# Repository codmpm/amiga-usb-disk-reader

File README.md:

# Amiga USB Floppy Disk Reader

> __abandoned in favor of https://nickslabor.niteto.de/projekte/adf-copy/__

This is a PCB I've designed to work with the marvelous idea, firmware and software 
from Rob Smith: https://github.com/RobSmithDev/ArduinoFloppyDiskReader 

It's nothing fancy but has some benefits I think that do matter:

* integrated _real_ FTDI232RL for communication and AVR flashing
* Decent DC/DC converter that can handle up to 5V/1A and wide input voltage (7-36V). 
This is the more power friendly way, as some drives demand more than the 
max. 500mA USB delivers
* Switchable to USB power if desired
* ATMega 328p on board with [Optiboot](https://github.com/Optiboot/optiboot)
* Solderpads for 4-pin Molex 3.5" connector with routed VCC. So if the drive needs 12V you 
can use a 12V power source

Of course this is only a fun project and does not aim to be the _best_ solution for Rob's 
approach, but it made my life easier.

This is the first release, as the PCB's have to be tested. I'm currently waiting for the 
prototypes.

## PCB

## Contributing

1. Fork it!
2. Create your feature branch: `git checkout -b my-new-feature`
3. Commit your changes: `git commit -am 'Add some feature'`
4. Push to the branch: `git push origin my-new-feature`
5. Submit a pull request :D

## Credits
Patrik Mayer, cod.m GmbH, 2019 

Rob Smith, who had the initial idea and wrote the software this is using

## License
[CC-BY-SA](https://creativecommons.org/licenses/by-sa/3.0/)

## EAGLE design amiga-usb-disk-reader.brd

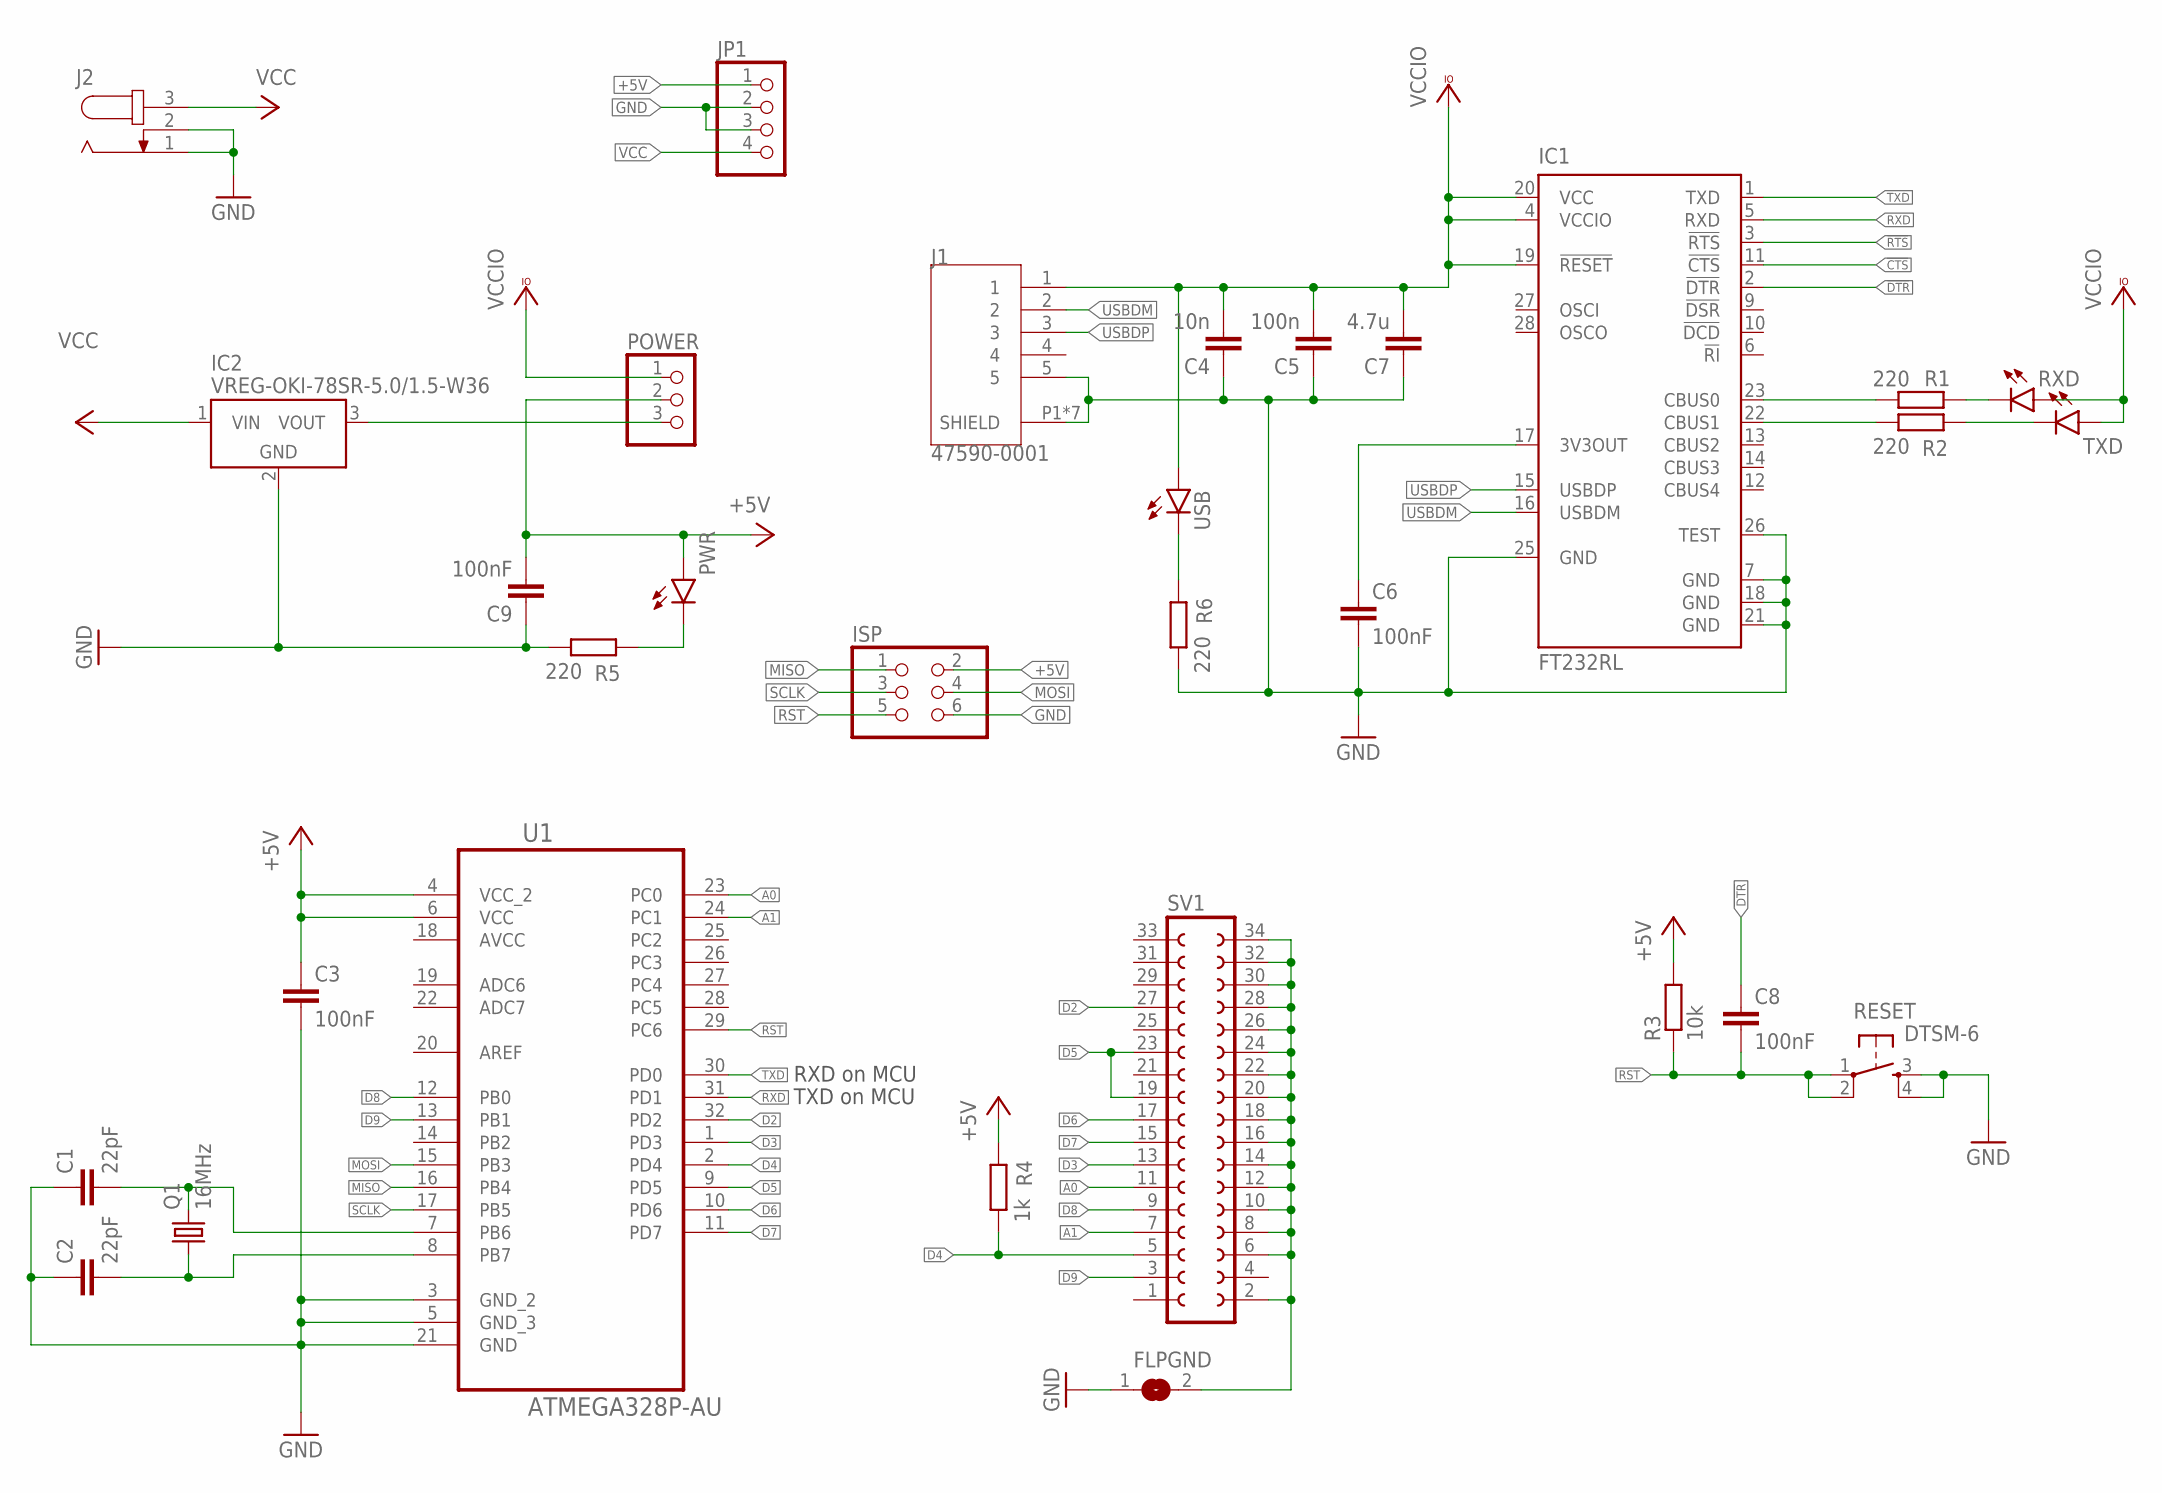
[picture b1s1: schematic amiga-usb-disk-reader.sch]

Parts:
C1, C2: 22pF; C0805
C3, C6, C8, C9: 100nF; C0805
C4: 10n; C0805
C5: 100n; C0805
C7: 4.7u; C0805
FLPGND: SJ
IC1: FT232RL; SSOP28
IC2: VREG-OKI-78SR-5.0/1.5-W36; OKI-78SR
ISP: PINHD-2X3; 2X03
J1: 47590-0001; MOLEX_47590-0001
J2: JACK-PLUG0; SPC4077
JP1: PINHD-1X4; 1X04
POWER: PINHD-1X3; 1X03
PWR: LEDSML0805; SML0805
Q1: 16MHz; HC49U70
R1, R2, R5, R6: 220; R0805
R3: 10k; R0805
R4: 1k; R0805
RESET: DTSM-6
RXD: LEDSML0805; SML0805
SV1: FE17-2W
TXD: LEDSML0805; SML0805
U1: ATMEGA328P-AU; QFP80P900X900X120-32N
USB: LEDSML0805; SML0805

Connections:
!CTS: IC1.11 (!CTS)
!DTR: C8.1, IC1.2 (!DTR)
!RTS: IC1.3 (!RTS)
+5V: C3.1, C9.2, ISP.2, JP1.1, POWER.2, PWR.A, R3.2, R4.1, U1.4 (VCC_2), U1.6 (VCC)
A0: SV1.11, U1.23 (PC0)
A1: SV1.7, U1.24 (PC1)
AVCC: U1.18 (AVCC)
CBUS0: IC1.23 (CBUS0), R1.2
CBUS1: IC1.22 (CBUS1), R2.2
D2: SV1.27, U1.32 (PD2)
D3: SV1.13, U1.1 (PD3)
D4: R4.2, SV1.5, U1.2 (PD4)
D5: SV1.19, SV1.23, U1.9 (PD5)
D6: SV1.17, U1.10 (PD6)
D7: SV1.15, U1.11 (PD7)
D8: SV1.9, U1.12 (PB0)
D9: SV1.3, U1.13 (PB1)
GND: C1.1, C2.1, C3.2, C4.1, C5.1, C6.2, C7.1, C9.1, FLPGND.1, IC1.7 (GND), IC1.18 (GND), IC1.21 (GND), IC1.25 (GND), IC1.26 (TEST), IC2.2 (GND), ISP.6, J1.5, J1.P1 (SHIELD), J1.P2 (SHIELD), J1.P3 (SHIELD), J1.S1 (SHIELD), J1.S2 (SHIELD), J1.S3 (SHIELD), J1.S4 (SHIELD), J2.1, J2.2, JP1.2, JP1.3, R5.2, R6.2, RESET.3, RESET.4, U1.3 (GND_2), U1.5 (GND_3), U1.21 (GND)
MISO: ISP.1, U1.16 (PB4)
MOSI: ISP.4, U1.15 (PB3)
unnamed: C6.1, IC1.17 (3V3OUT)
unnamed: C2.2, Q1.1, U1.8 (PB7)
unnamed: C1.2, Q1.2, U1.7 (PB6)
unnamed: FLPGND.2, SV1.2, SV1.6, SV1.8, SV1.10, SV1.12, SV1.14, SV1.16, SV1.18, SV1.20, SV1.22, SV1.24, SV1.26, SV1.28, SV1.30, SV1.32, SV1.34
unnamed: R2.1, TXD.C
unnamed: R1.1, RXD.C
unnamed: PWR.C, R5.1
unnamed: IC2.3 (VOUT), POWER.3
unnamed: R6.1, USB.C
RST: C8.2, ISP.5, R3.1, RESET.1, RESET.2
RXD: IC1.5 (RXD), U1.31 (PD1)
SCLK: ISP.3, U1.17 (PB5)
TXD: IC1.1 (TXD), U1.30 (PD0)
USBDM: IC1.16 (USBDM), J1.2
USBDP: IC1.15 (USBDP), J1.3
VCC: IC2.1 (VIN), J2.3, JP1.4
VCCIO: C4.2, C5.2, C7.2, IC1.4 (VCCIO), IC1.19 (!RESET), IC1.20 (VCC), J1.1, POWER.1, RXD.A, TXD.A, USB.A

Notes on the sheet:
RXD on MCU
TXD on MCU

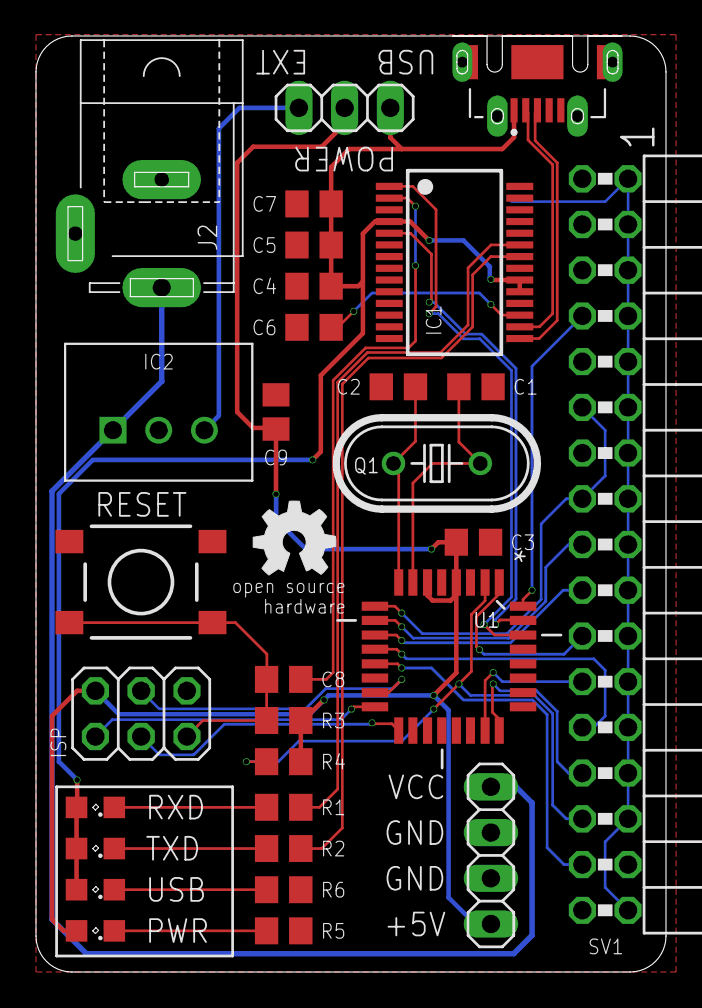
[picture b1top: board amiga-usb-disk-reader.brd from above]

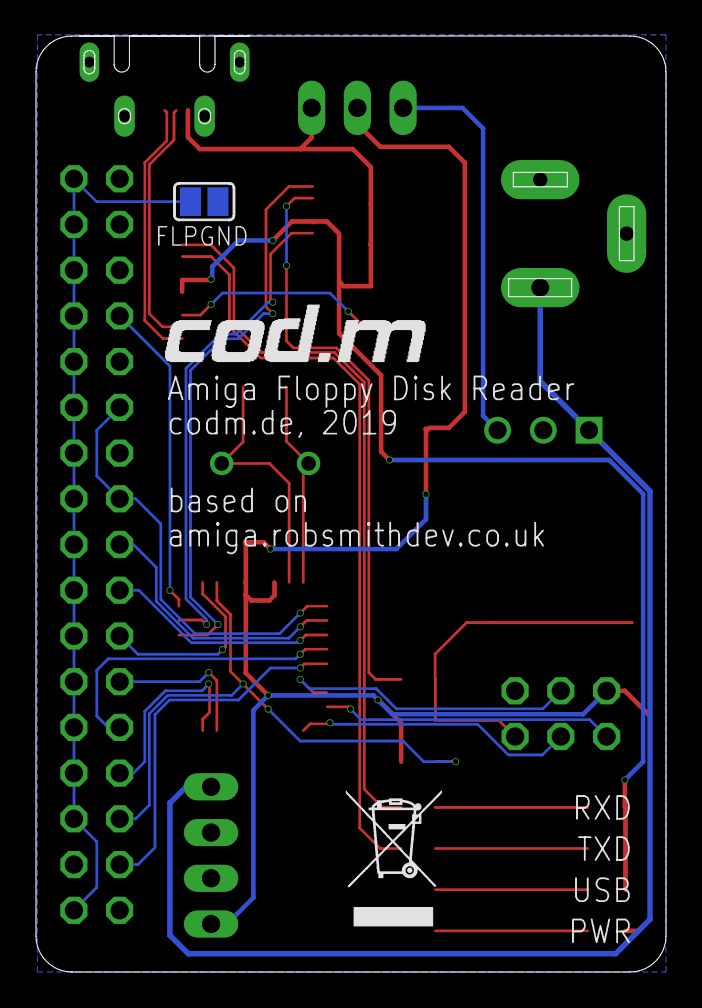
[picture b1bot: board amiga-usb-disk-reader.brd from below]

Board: 2 copper layers, 35.0 x 52.0 mm, 34 parts (3 on the bottom side), 34 nets.

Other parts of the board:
U$1: OSHW_5MM
U$2: WEEE-LOGO-5MM
U$3: CODM-LOGO

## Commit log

2019-02-13 initial release
2019-02-13 fixed images in readme
2019-02-13 optimized images
2019-02-13 refined readme
